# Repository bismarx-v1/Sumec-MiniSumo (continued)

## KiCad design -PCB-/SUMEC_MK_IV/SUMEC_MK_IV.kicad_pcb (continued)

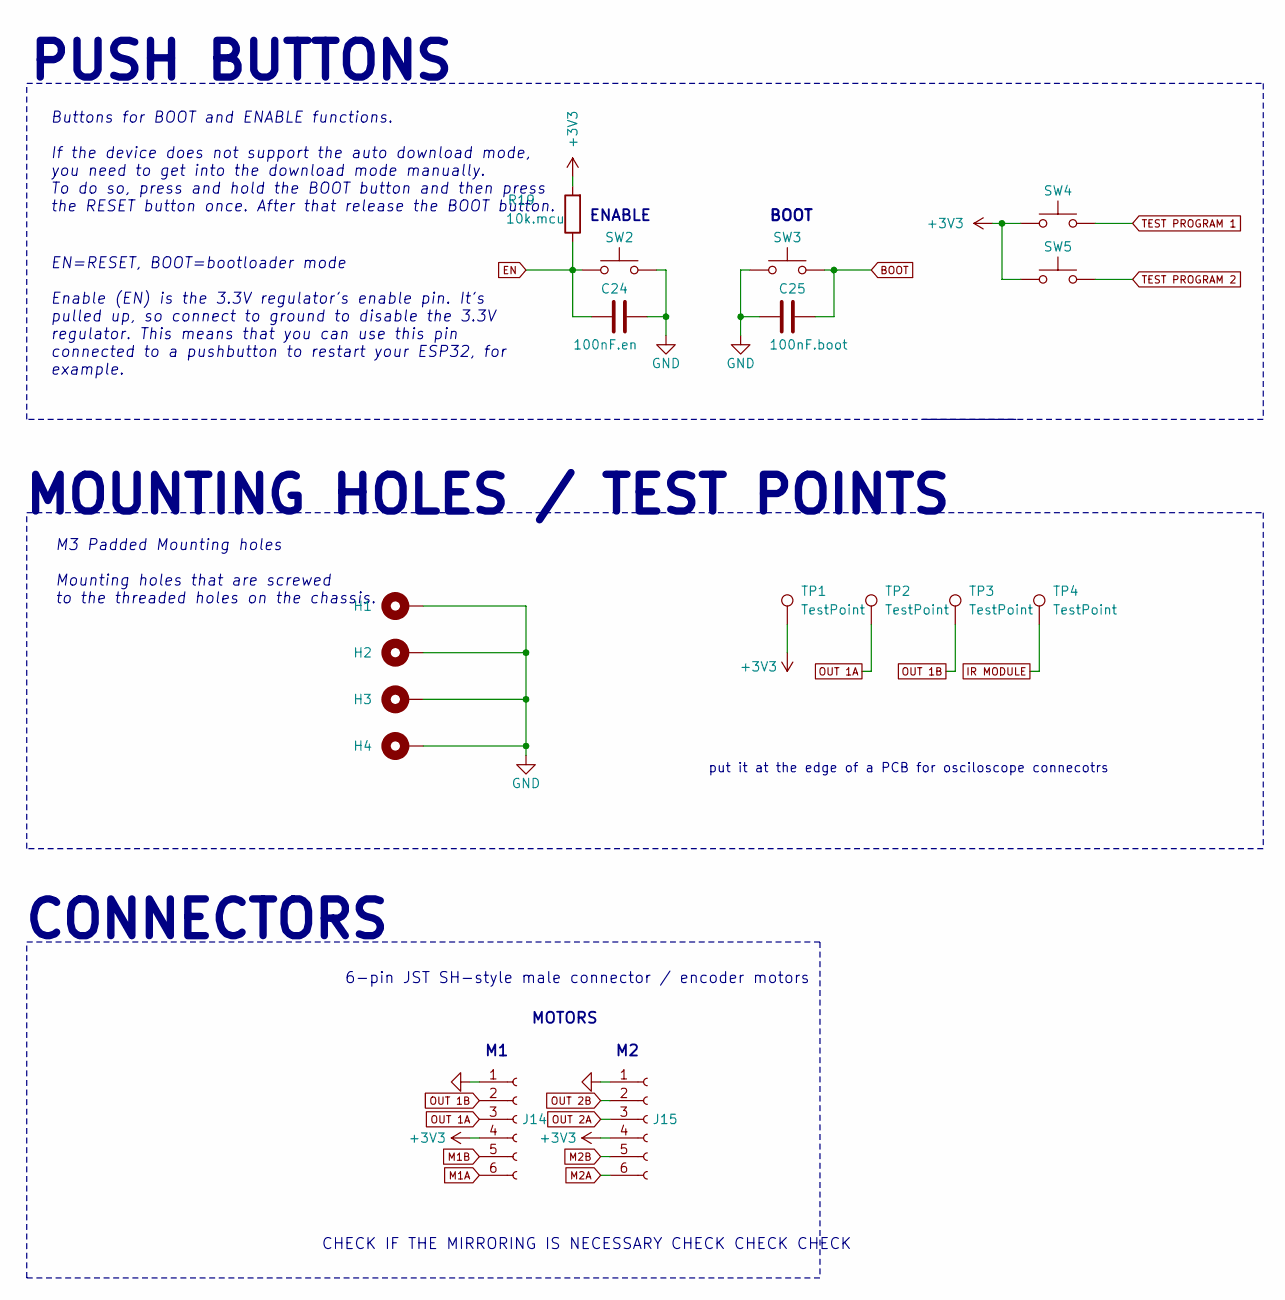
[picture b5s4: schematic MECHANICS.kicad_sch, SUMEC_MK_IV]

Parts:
C24: 100nF.en; C_0805_2012Metric_Pad1.18x1.45mm_HandSolder
C25: 100nF.boot; C_0805_2012Metric_Pad1.18x1.45mm_HandSolder
H1, H2, H3, H4: Mounting Hole M3; MountingHole_3.2mm_M3_Pad_Via
J14, J15: Conn_01x06_Socket; JST_SH_SM06B-SRSS-TB_1x06-1MP_P1.00mm_Horizontal
R19: 10k.mcu; R_0805_2012Metric_Pad1.20x1.40mm_HandSolder
SW2, SW3, SW4, SW5: SW_Push; SW_SPST_EVQPE1
TP1, TP2, TP3, TP4: TestPoint; TestPoint_Pad_1.0x1.0mm

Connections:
+3V3: J14.4, J15.4, R19.2, SW4.1, SW5.1, TP1.1; also elsewhere on the board
BOOT: C25.1, SW3.2; also elsewhere on the board
EN: C24.1, R19.1, SW2.2; also elsewhere on the board
GND: C24.2, C25.2, H1.1, H2.1, H3.1, H4.1, J14.1, J15.1, SW2.1, SW3.1; also elsewhere on the board
IR MODULE: TP4.1; also elsewhere on the board
M1A: J14.6; also elsewhere on the board
M1B: J14.5; also elsewhere on the board
M2A: J15.6; also elsewhere on the board
M2B: J15.5; also elsewhere on the board
OUT 1A: J14.3, TP2.1; also elsewhere on the board
OUT 1B: J14.2, TP3.1; also elsewhere on the board
OUT 2A: J15.3; also elsewhere on the board
OUT 2B: J15.2; also elsewhere on the board
TEST PROGRAM 1: SW4.2; also elsewhere on the board
TEST PROGRAM 2: SW5.2; also elsewhere on the board

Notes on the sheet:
put it at the edge of a PCB for osciloscope connecotrs
PUSH BUTTONS
CHECK IF THE MIRRORING IS NECESSARY CHECK CHECK CHECK
M3 Padded Mounting holes Mounting holes that are screwed to the threaded holes on the chassis.
ENABLE
EN=RESET, BOOT=bootloader mode Enable (EN) is the 3.3V regulator's enable pin. It's pulled up, so connect to ground to disable the 3.3V regulator. This means that you can use this pin connected to a pushbutton to restart your ESP32, for example.
Buttons for BOOT and ENABLE functions. If the device does not support the auto download mode, you need to get into the download mode manually. To do so, press and hold the BOOT button and then press the RESET button once. After that release the BOOT button.
BOOT
CONNECTORS
6-pin JST SH-style male connector / encoder motors
MOUNTING HOLES / TEST POINTS
MOTORS

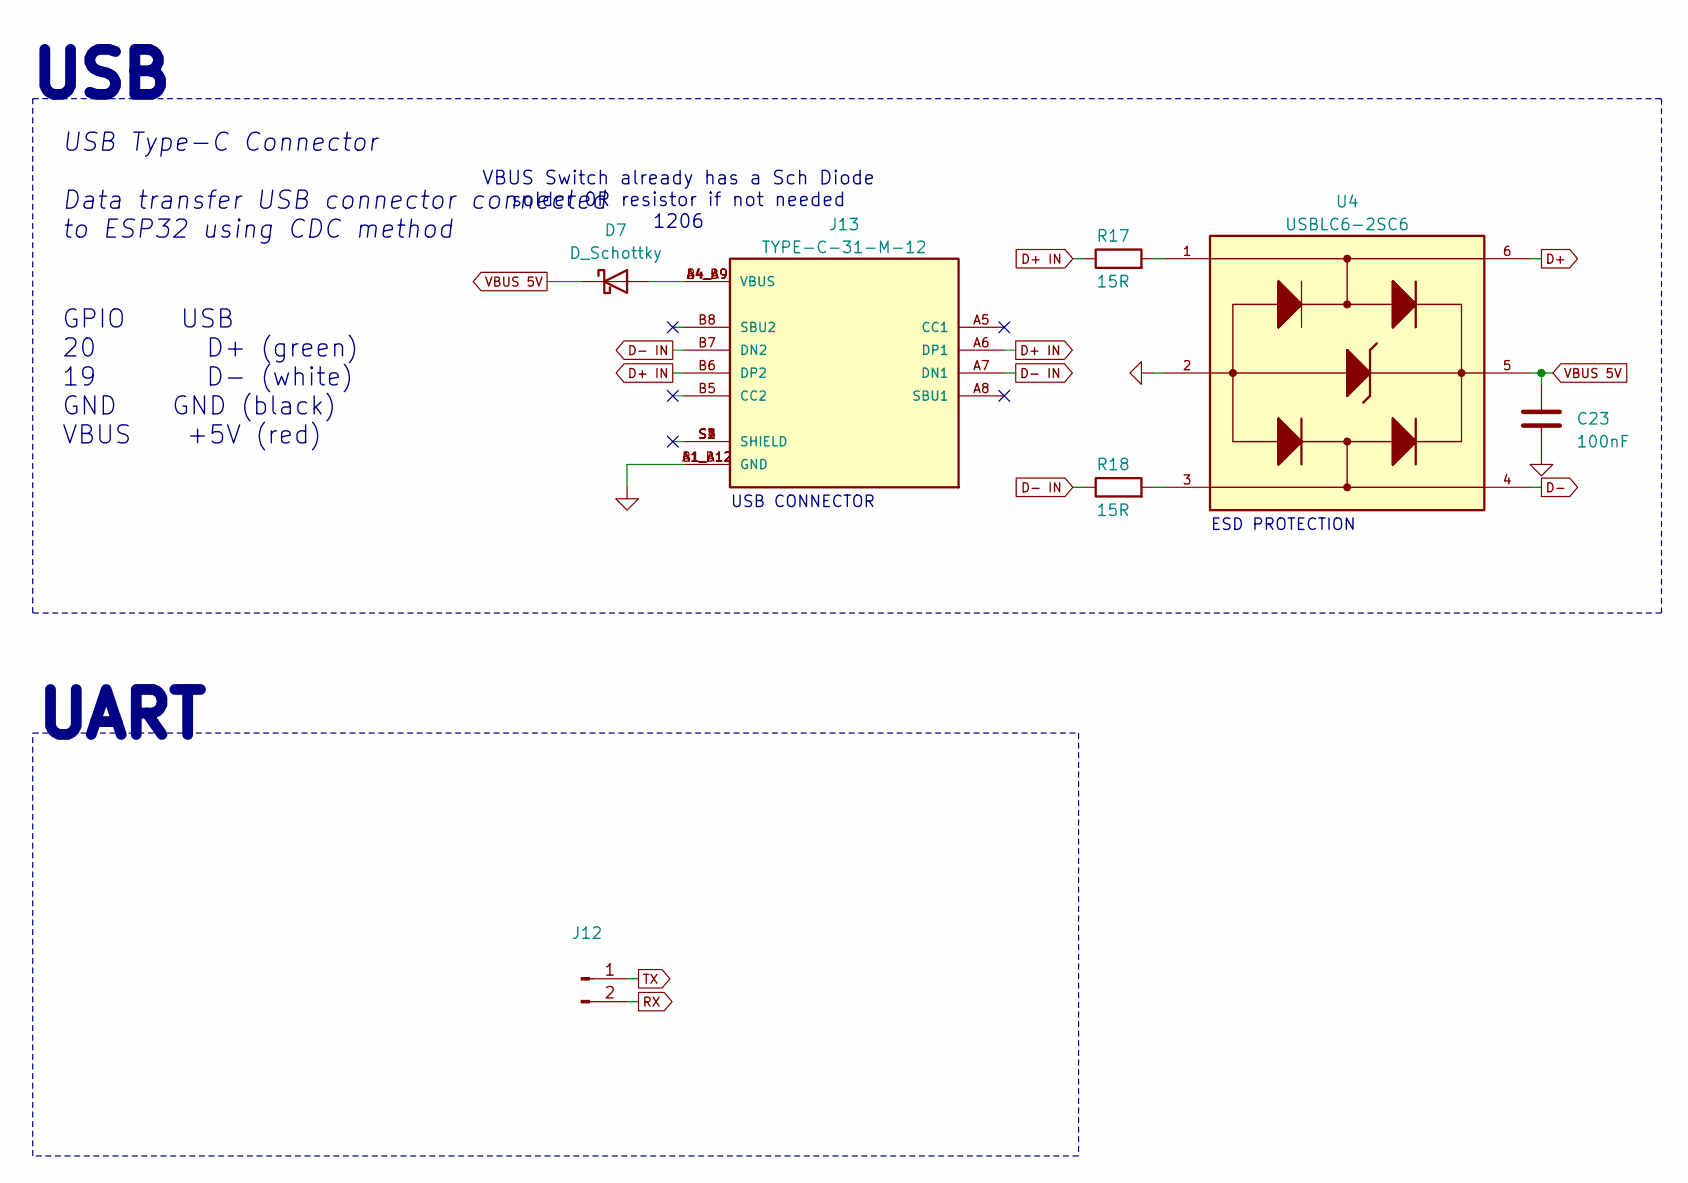
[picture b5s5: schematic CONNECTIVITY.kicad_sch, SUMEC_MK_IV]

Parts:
C23: 100nF; C_0805_2012Metric_Pad1.18x1.45mm_HandSolder
D7: D_Schottky; D_1206_3216Metric_Pad1.42x1.75mm_HandSolder
J12: Conn_01x02_Pin; TestPoint_2Pads_Pitch2.54mm_Drill0.8mm
J13: TYPE-C-31-M-12; USB_Type_C; PARTREV 2020.12.08
R17, R18: 15R; R_0805_2012Metric_Pad1.20x1.40mm_HandSolder
U4: USBLC6-2SC6; TSOT-23-6_HandSoldering

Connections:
D+: U4.6; also elsewhere on the board
D+ IN: J13.A6 (DP1), J13.B6 (DP2), R17.1
D-: U4.4; also elsewhere on the board
D- IN: J13.A7 (DN1), J13.B7 (DN2), R18.1
GND: C23.2, J13.A1_B12 (GND), J13.B1_A12 (GND), U4.2; also elsewhere on the board
unnamed: D7.2 (A), J13.A4_B9 (VBUS), J13.B4_A9 (VBUS)
unnamed: R17.2, U4.1
unnamed: R18.2, U4.3
RX: J12.2; also elsewhere on the board
TX: J12.1; also elsewhere on the board
VBUS 5V: C23.1, D7.1 (K), U4.5; also elsewhere on the board

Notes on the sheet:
VBUS Switch already has a Sch Diode solder 0R resistor if not needed 1206
USB
GPIO USB 20 D+ (green) 19 D- (white) GND GND (black) VBUS +5V (red)
USB CONNECTOR
USB Type-C Connector Data transfer USB connector connected to ESP32 using CDC method
UART
ESD PROTECTION

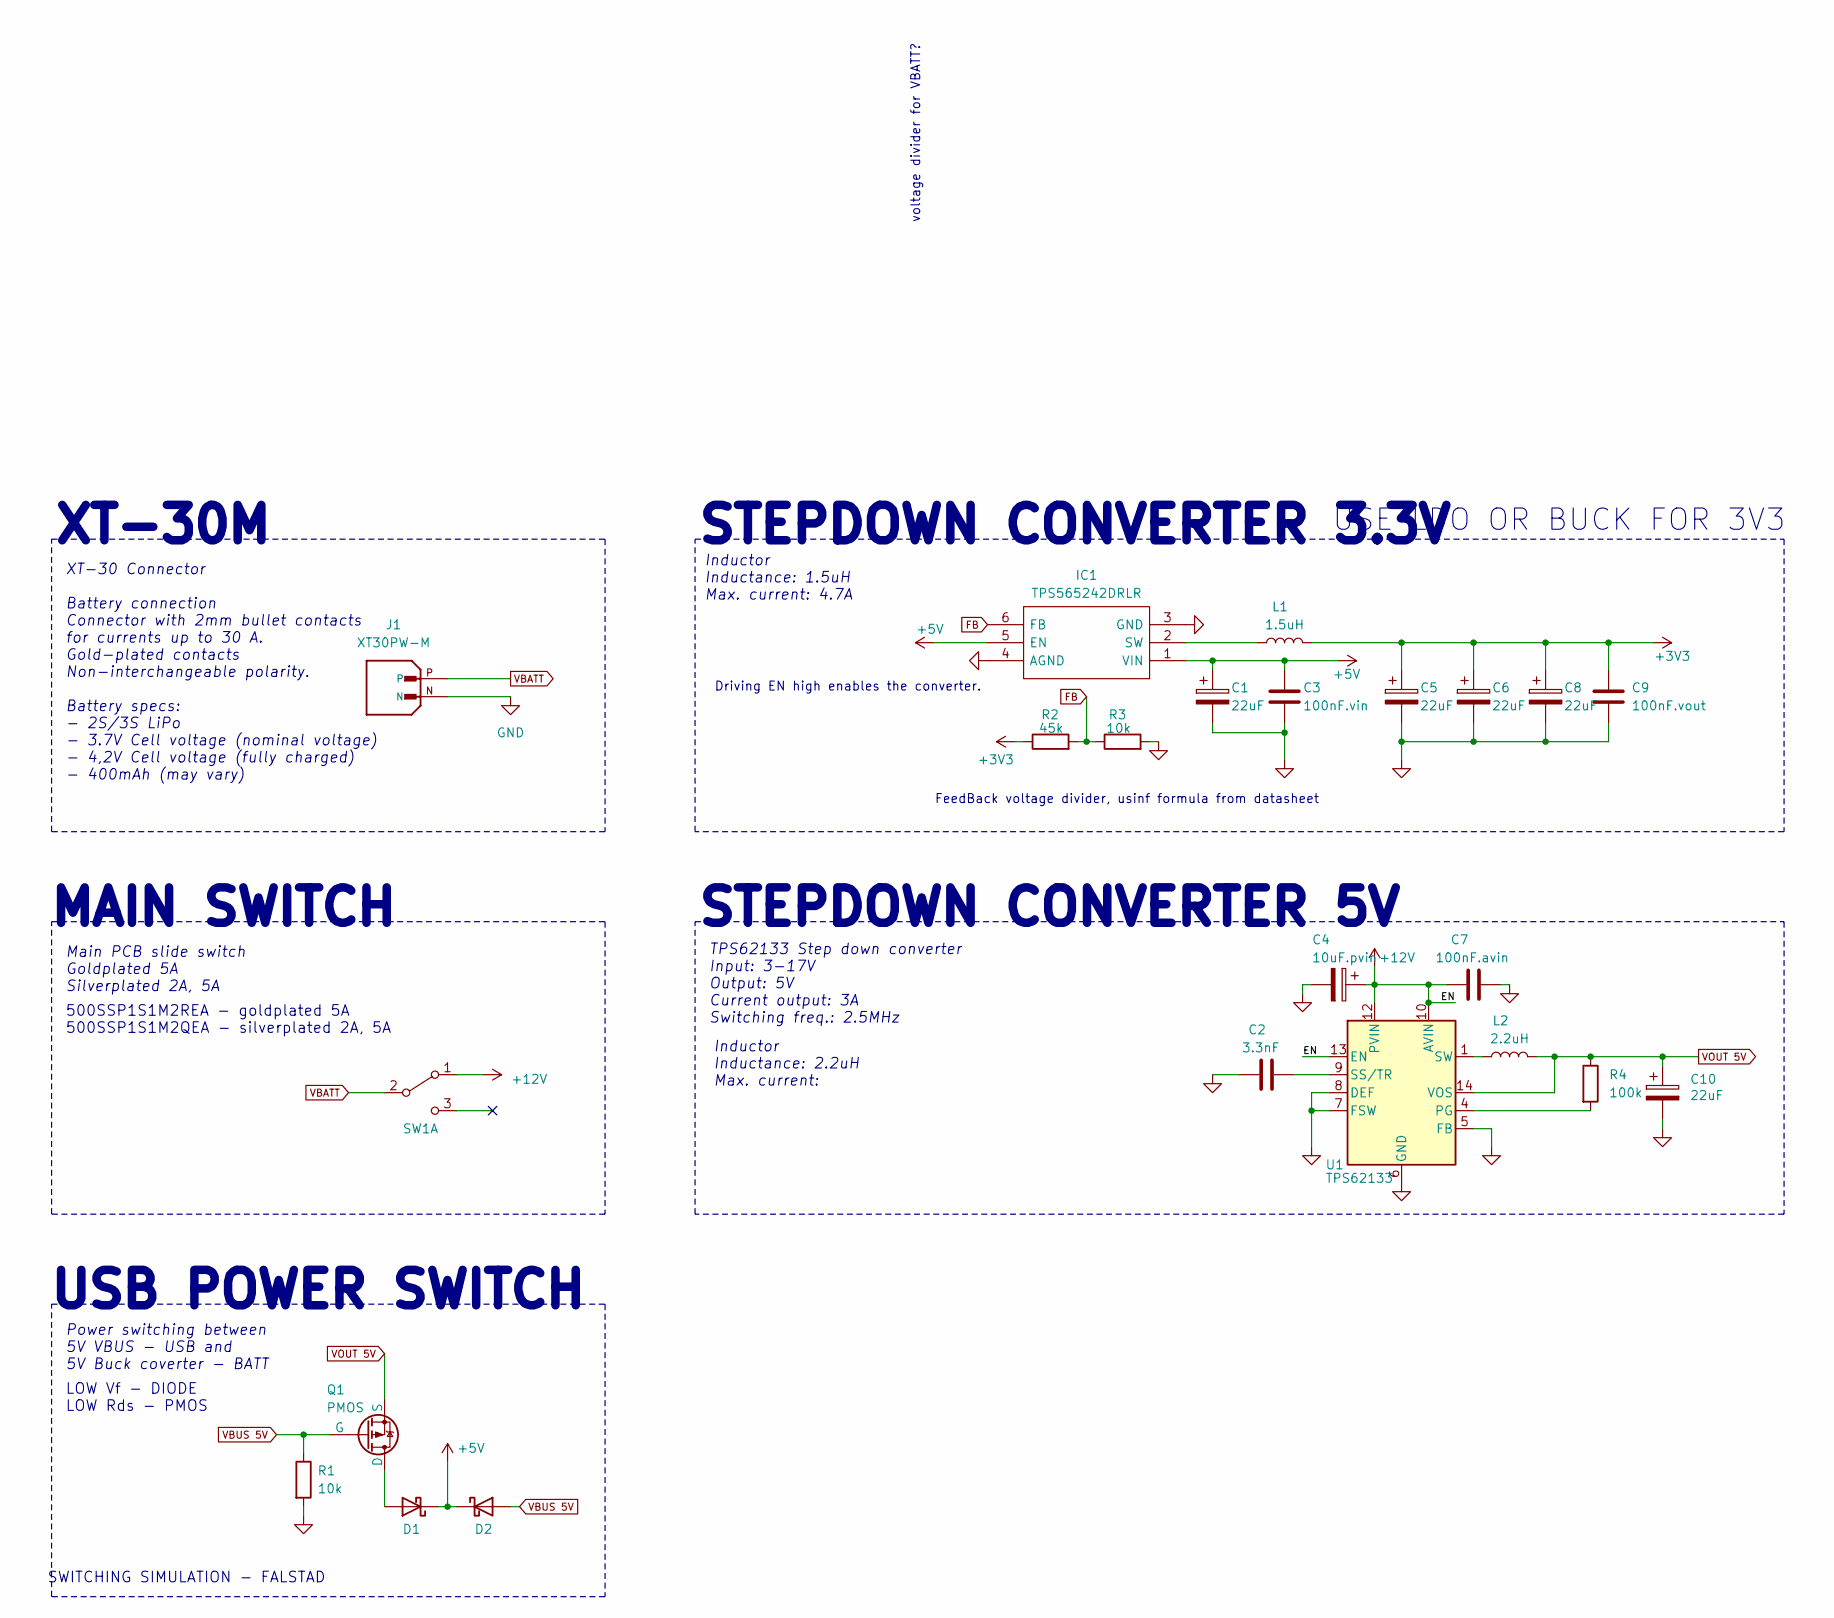
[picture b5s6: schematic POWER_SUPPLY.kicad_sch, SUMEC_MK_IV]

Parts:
C1, C5, C6, C8, C10: 22uF; CP_EIA-2012-12_Kemet-R_Pad1.30x1.05mm_HandSolder
C2: 3.3nF; C_0805_2012Metric_Pad1.18x1.45mm_HandSolder
C3: 100nF.vin; C_0805_2012Metric_Pad1.18x1.45mm_HandSolder; LCSC C49678
C4: 10uF.pvin; CP_EIA-3216-18_Kemet-A_Pad1.58x1.35mm_HandSolder
C7: 100nF.avin; C_0805_2012Metric_Pad1.18x1.45mm_HandSolder
C9: 100nF.vout; C_0805_2012Metric_Pad1.18x1.45mm_HandSolder; LCSC C49678
D1, D2: D_Schottky; D_1206_3216Metric_Pad1.42x1.75mm_HandSolder
IC1: TPS565242DRLR; SOT-563; Manufacturer_Part_Number TPS565242DRLR; Mouser Part Number 595-TPS565242DRLR
J1: XT30PW-M; PARTREV 1.2
L1: 1.5uH; L_Vishay_IHLP-1212
L2: 2.2uH; L_Vishay_IHLP-1616
Q1: PMOS; SOT-23-3
R1: 10k; R_0805_2012Metric_Pad1.20x1.40mm_HandSolder
R2: 45k; R_0805_2012Metric_Pad1.20x1.40mm_HandSolder; LCSC C17470
R3: 10k; R_0805_2012Metric_Pad1.20x1.40mm_HandSolder; LCSC C17633
R4: 100k; R_0805_2012Metric_Pad1.20x1.40mm_HandSolder
SW1: SW_DPDT_x2; Custom_SPDT_4.7mm_Switch
U1: TPS62133; VQFN-16-1EP_3x3mm_P0.5mm_EP1.68x1.68mm_ThermalVias

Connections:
+3V3: C5.1, C6.1, C8.1, C9.1, L1.2, R2.1; also elsewhere on the board
+5V: C1.1, C3.1, D1.1 (K), D2.1 (K), IC1.1 (VIN), IC1.5 (EN); also elsewhere on the board
+12V: C4.1, C7.1, SW1.1 (A), U1.10 (AVIN), U1.11 (PVIN), U1.12 (PVIN), U1.13 (EN); also elsewhere on the board
FB: IC1.6 (FB), R2.2, R3.1
GND: C1.2, C2.1, C3.2, C4.2, C5.2, C6.2, C7.2, C8.2, C9.2, C10.2, IC1.3 (GND), IC1.4 (AGND), J1.N, R1.2, R3.2, U1.5 (FB), U1.6 (GND), U1.7 (FSW), U1.8 (DEF), U1.15 (GND), U1.16 (GND), U1.17 (GND); also elsewhere on the board
unnamed: D1.2 (A), Q1.1 (D)
unnamed: IC1.2 (SW), L1.1
unnamed: L2.1, U1.1 (SW), U1.2 (SW), U1.3 (SW)
unnamed: R4.2, U1.4 (PG)
unnamed: C2.2, U1.9 (SS/TR)
VBATT: J1.P, SW1.2 (B)
VBUS 5V: D2.2 (A), Q1.2 (G), R1.1; also elsewhere on the board
VOUT 5V: C10.1, L2.2, Q1.3 (S), R4.1, U1.14 (VOS)

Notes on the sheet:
Inductor Inductance: 2.2uH Max. current:
SWITCHING SIMULATION - FALSTAD
Driving EN high enables the converter.
USB POWER SWITCH
XT-30M
LOW Vf - DIODE LOW Rds - PMOS
Power switching between 5V VBUS - USB and 5V Buck coverter - BATT
MAIN SWITCH
voltage divider for VBATT?
500SSP1S1M2REA - goldplated 5A 500SSP1S1M2QEA - silverplated 2A, 5A
Main PCB slide switch Goldplated 5A Silverplated 2A, 5A
STEPDOWN CONVERTER 3.3V
STEPDOWN CONVERTER 5V
Inductor Inductance: 1.5uH Max. current: 4.7A
TPS62133 Step down converter Input: 3-17V Output: 5V Current output: 3A Switching freq.: 2.5MHz
FeedBack voltage divider, usinf formula from datasheet
XT-30 Connector Battery connection Connector with 2mm bullet contacts for currents up to 30 A. Gold-plated contacts Non-interchangeable polarity. Battery specs: - 2S/3S LiPo - 3.7V Cell voltage (nominal voltage) - 4,2V Cell voltage (fully charged) - 400mAh (may vary)
USE LDO OR BUCK FOR 3V3

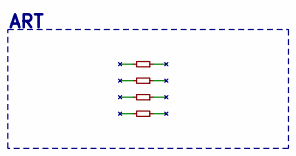
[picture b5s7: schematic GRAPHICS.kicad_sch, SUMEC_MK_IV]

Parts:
R20: R; purosidenegative
R21: R; SPS LOGO
R22: R; boi
R23: R; Logo

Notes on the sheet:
ART

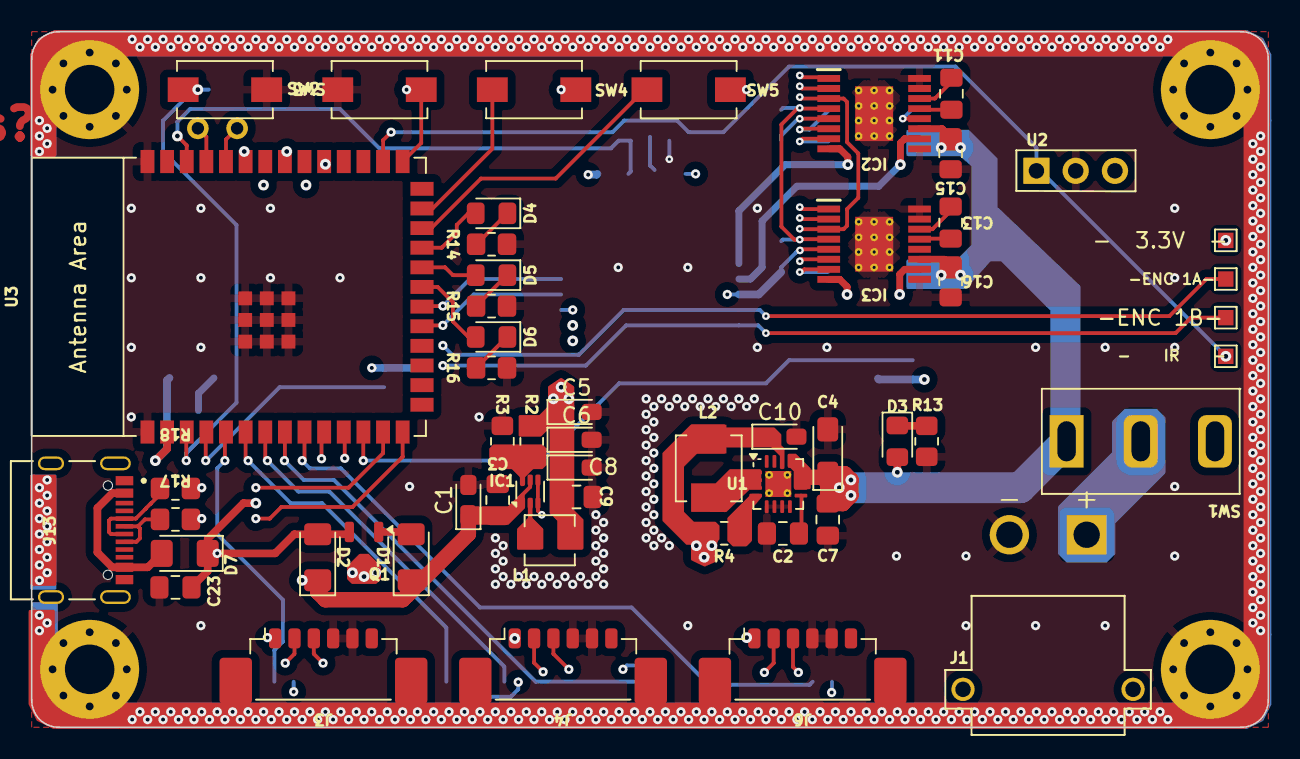
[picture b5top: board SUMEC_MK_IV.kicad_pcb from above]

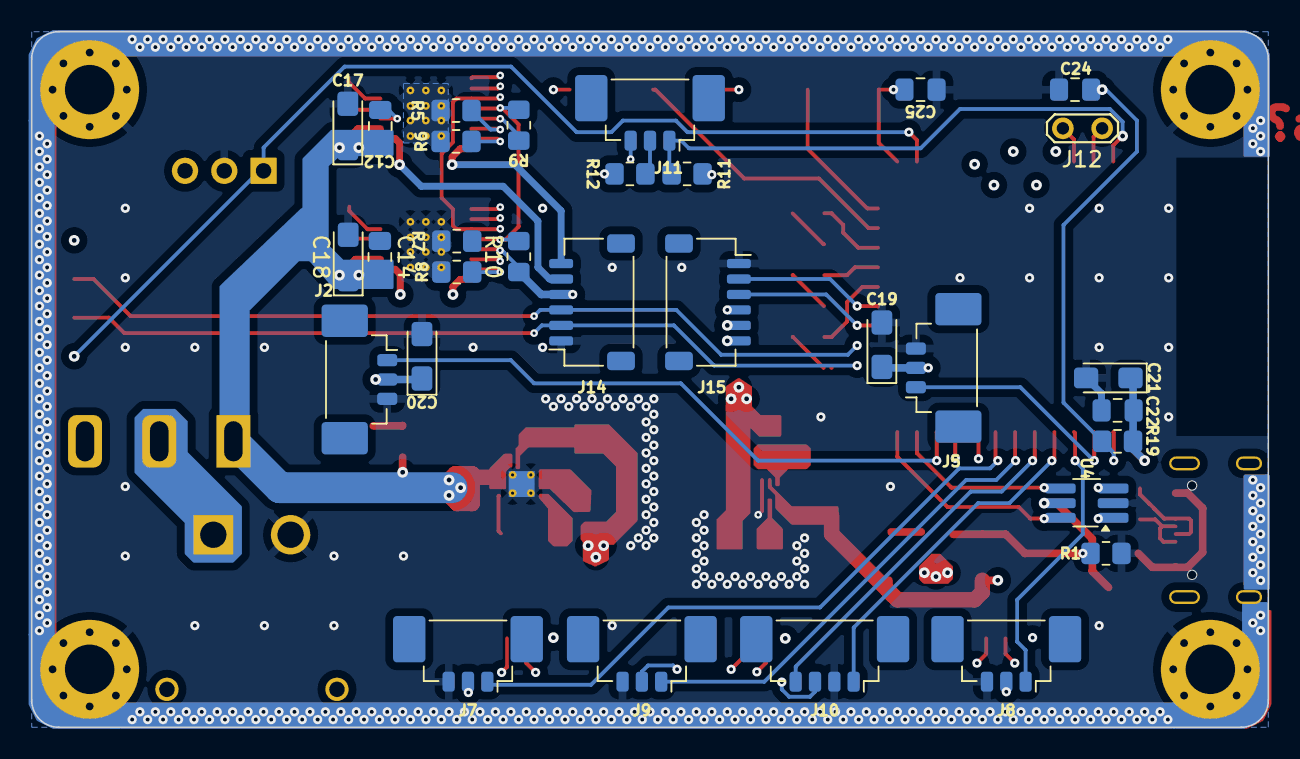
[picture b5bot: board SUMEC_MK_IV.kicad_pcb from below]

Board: 4 copper layers, 80.0 x 45.0 mm, 93 parts (31 on the bottom side), 68 nets.

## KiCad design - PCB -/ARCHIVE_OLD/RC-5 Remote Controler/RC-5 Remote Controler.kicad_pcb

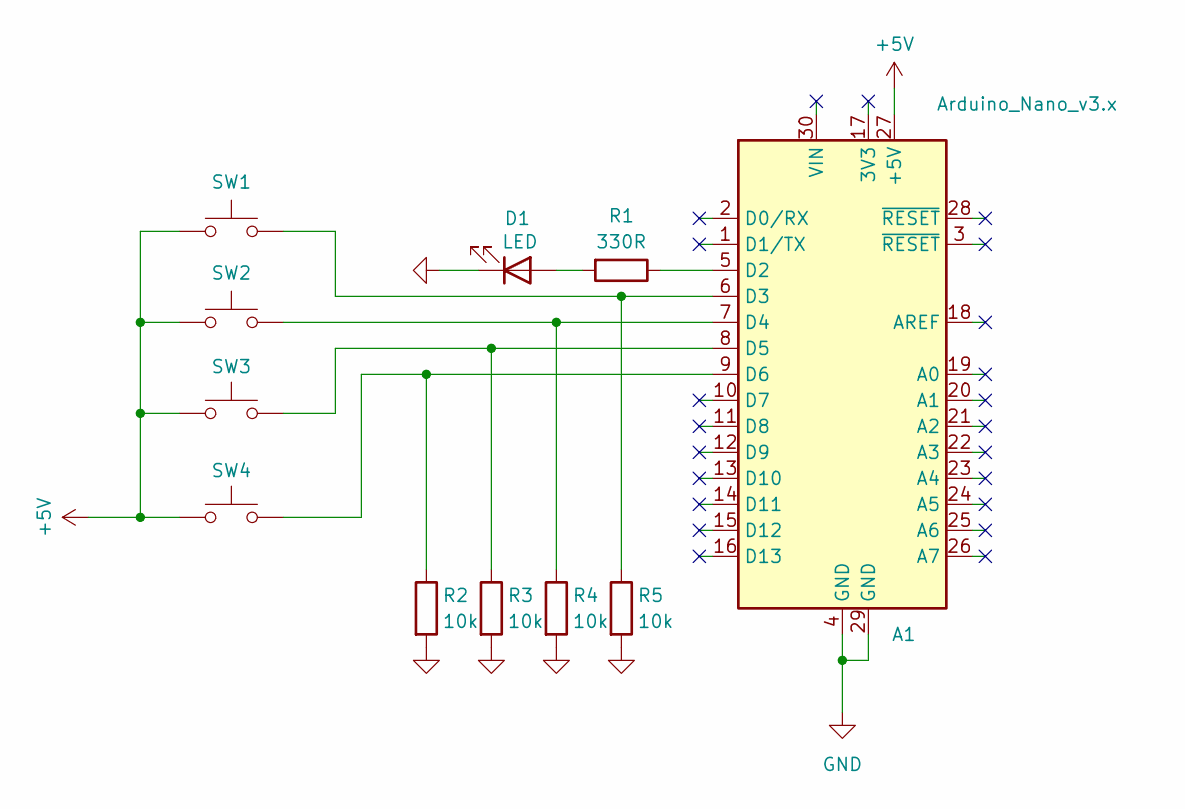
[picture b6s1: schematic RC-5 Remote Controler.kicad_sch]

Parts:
A1: Arduino_Nano_v3.x; Arduino_Nano
D1: LED; LED_D3.0mm_Horizontal_O3.81mm_Z6.0mm
R1: 330R; R_Axial_DIN0207_L6.3mm_D2.5mm_P10.16mm_Horizontal
R2, R3, R4, R5: 10k; R_Axial_DIN0207_L6.3mm_D2.5mm_P10.16mm_Horizontal
SW1, SW2, SW3, SW4: SW_Push; SW_PUSH_6mm

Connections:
+5V: A1.27 (+5V), SW1.1, SW2.1, SW3.1, SW4.1
GND: A1.4 (GND), A1.29 (GND), D1.1 (K), R2.2, R3.2, R4.2, R5.2
unnamed: A1.5 (D2), R1.1
unnamed: A1.6 (D3), R5.1, SW1.2
unnamed: A1.7 (D4), R4.1, SW2.2
unnamed: A1.8 (D5), R3.1, SW3.2
unnamed: A1.9 (D6), R2.1, SW4.2
unnamed: D1.2 (A), R1.2

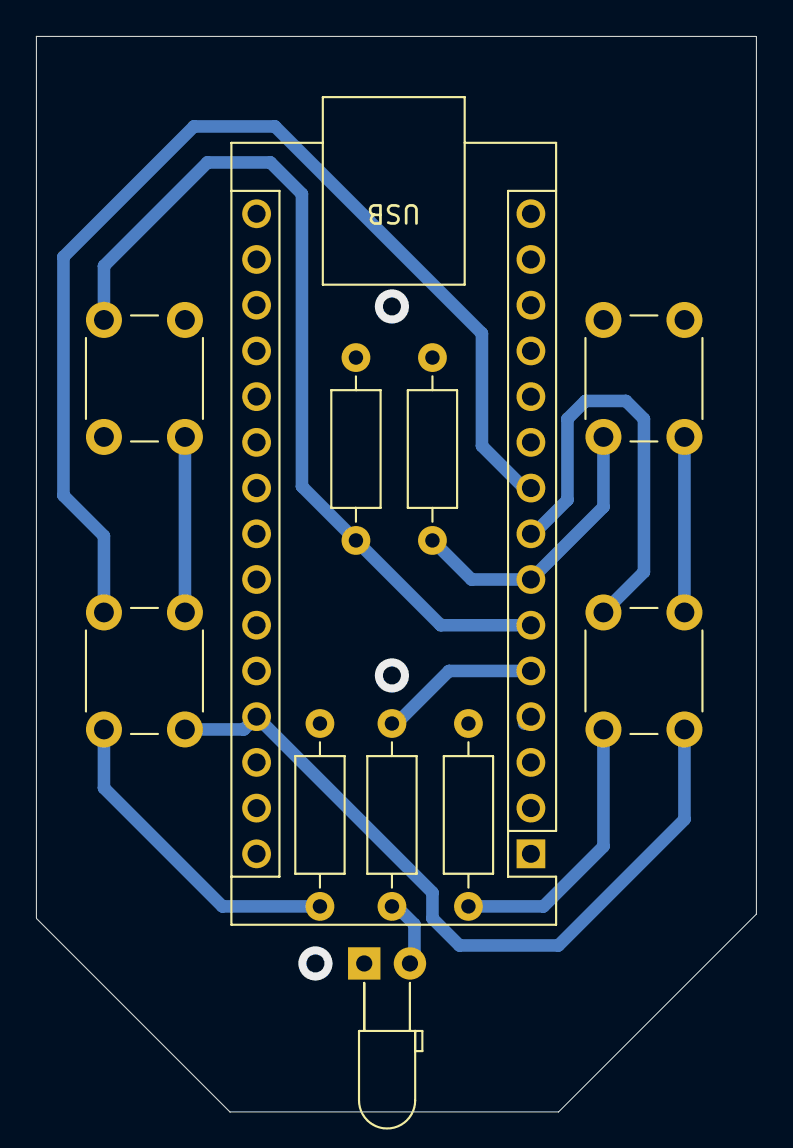
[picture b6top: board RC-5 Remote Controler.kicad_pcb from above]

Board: 2 copper layers, 40.0 x 59.8 mm, 11 parts (0 on the bottom side), 8 nets.

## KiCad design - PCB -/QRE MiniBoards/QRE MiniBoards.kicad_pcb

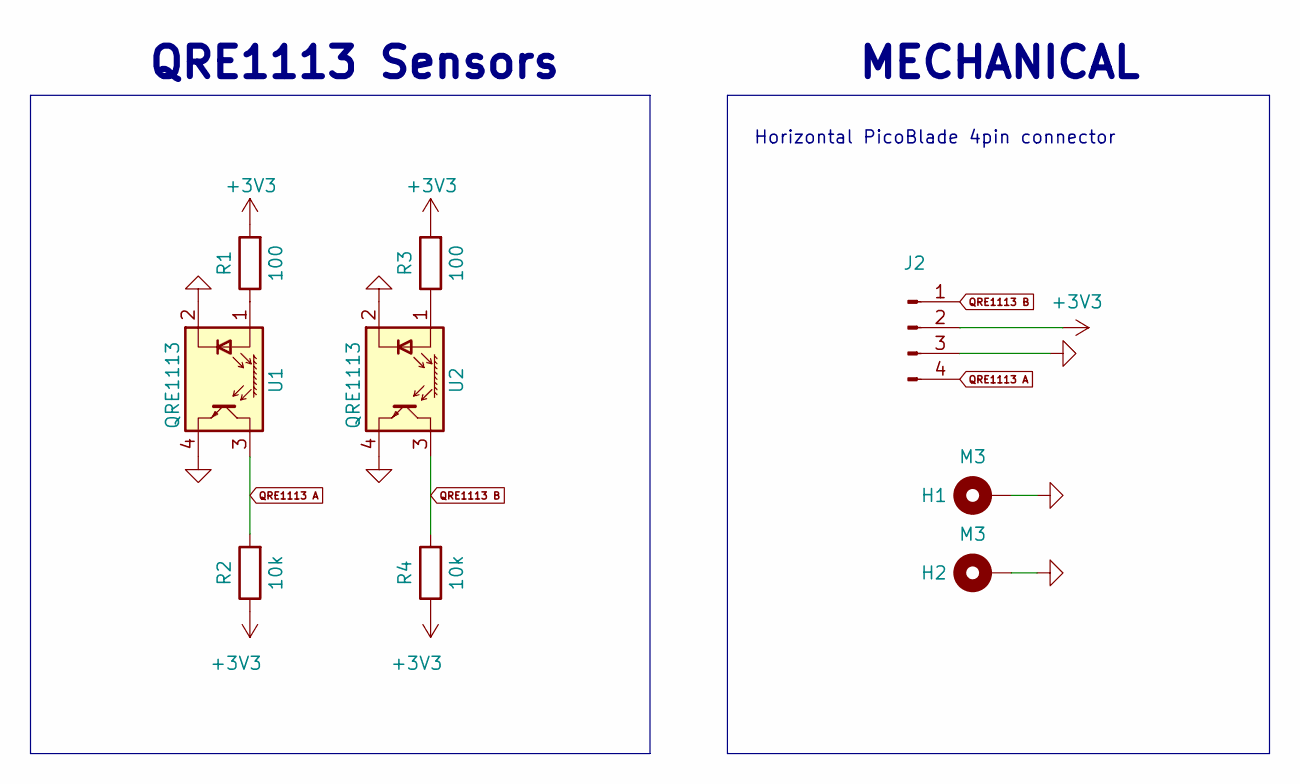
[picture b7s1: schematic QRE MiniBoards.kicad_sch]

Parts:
H1, H2: M3; MountingHole_3.2mm_M3_Pad
J2: Conn_01x04_Pin; Molex_PicoBlade_53261-0471_1x04-1MP_P1.25mm_Horizontal
R1, R3: 100; R_0805_2012Metric_Pad1.20x1.40mm_HandSolder
R2, R4: 10k; R_0805_2012Metric_Pad1.20x1.40mm_HandSolder
U1, U2: QRE1113; OnSemi_CASE100AQ - QRE1113

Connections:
+3V3: J2.2, R1.2, R2.1, R3.2, R4.1
GND: H1.1, H2.1, J2.3, U1.2 (K), U1.4, U2.2 (K), U2.4
unnamed: R1.1, U1.1 (A)
unnamed: R3.1, U2.1 (A)
QRE1113 A: J2.4, R2.2, U1.3
QRE1113 B: J2.1, R4.2, U2.3

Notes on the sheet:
QRE1113 Sensors
Horizontal PicoBlade 4pin connector
MECHANICAL

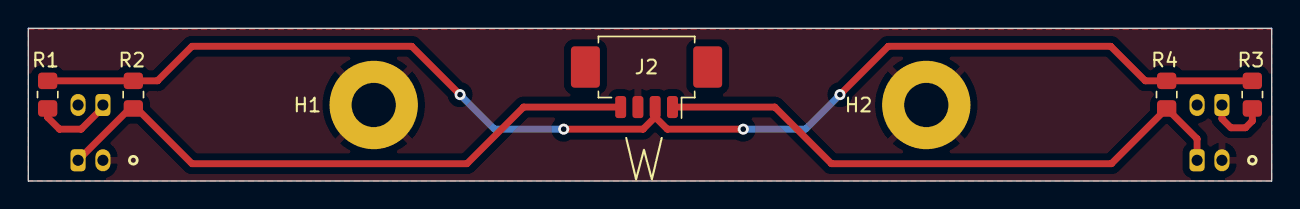
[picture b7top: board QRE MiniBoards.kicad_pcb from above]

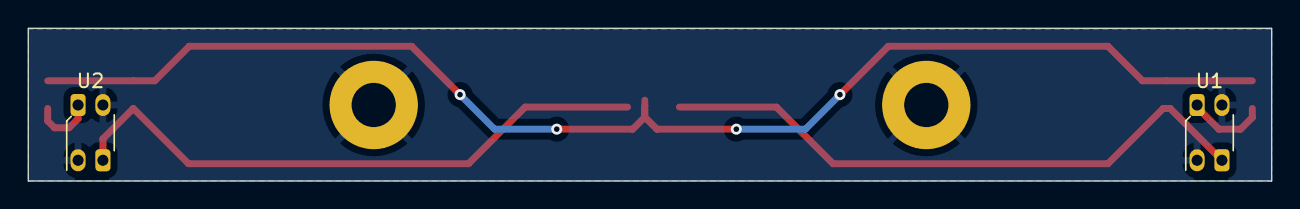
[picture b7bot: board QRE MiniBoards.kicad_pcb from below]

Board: 2 copper layers, 90.0 x 11.0 mm, 9 parts (2 on the bottom side), 6 nets.

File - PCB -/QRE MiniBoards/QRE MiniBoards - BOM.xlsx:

Item | Qty | Reference(s) | Value | LibPart | Footprint | Link
1 | 2 | H1, H2 | M3 | MountingHole - Pad (GND) | MountingHole:MountingHole_3.2mm_M3_Pad | N/A
2 | 1 | J2 | Conn_01x04 | MOLEX PicoBlade 4pin | Connector_Molex:Molex_PicoBlade_53398-0471_1x04-1MP_P1.25mm_Vertical
3 | 2 | R1, R3 | 100R | Resistor SMD | Resistor_SMD:R_1206_3216Metric_Pad1.30x1.75mm_HandSolder
4 | 2 | R2, R4 | 10k | Resistor SMD | Resistor_SMD:R_1206_3216Metric_Pad1.30x1.75mm_HandSolder
5 | 2 | U1, U2 | N/A | QRE1113 THT | sumec_library:OnSemi_CASE100AQ - QRE1113
6
7 | 9
8
9
10
11
12
13
14
15
16
17
18
19
20
21
22
23
24
25
26
27
28
29
30
31
32
33
34
35

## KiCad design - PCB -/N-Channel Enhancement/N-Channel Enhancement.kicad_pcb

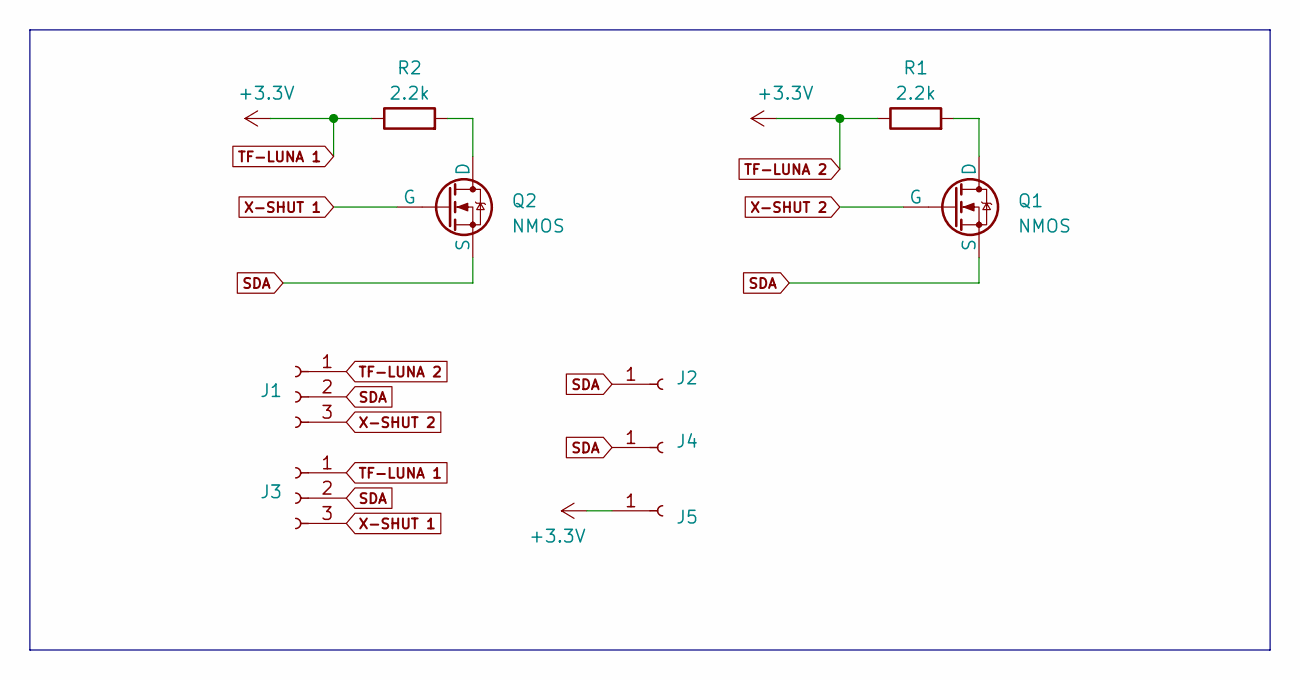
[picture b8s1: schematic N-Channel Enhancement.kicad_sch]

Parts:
J1, J3: Conn_01x03_Socket; PinSocket_1x03_P2.54mm_Vertical
J2, J4, J5: Conn_01x01_Socket; PinSocket_1x01_P2.54mm_Vertical
Q1, Q2: NMOS; SOT-23
R1, R2: 2.2k; R_Axial_DIN0207_L6.3mm_D2.5mm_P10.16mm_Horizontal

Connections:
unnamed: Q1.1 (D), R1.2
unnamed: Q2.1 (D), R2.2
SDA: J1.2, J2.1, J3.2, J4.1, Q1.3 (S), Q2.3 (S)
TF-LUNA 1: J1.1, J3.1, J5.1, R1.1, R2.1
X-SHUT 1: J3.3, Q2.2 (G)
X-SHUT 2: J1.3, Q1.2 (G)

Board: 2 copper layers, 9 parts (2 on the bottom side), 6 nets, no tracks yet.

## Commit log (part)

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2024-03-27 Driver test fix; Qre and Sharp libs pinMode fix
2024-03-27 tf-l set address and factory reset work, read and read distance do not
2024-03-28 qre_motors
2024-03-28 Fixed wrong value in a comment
2024-03-29 Čištění-github-CODE-mám zalohu
2024-03-29 NEW main code
2024-03-29 přidán hlavičkový soubor pro piny a proměné
2024-03-29 dodělání hlavičkového souboru pinů a proměných
2024-03-30 přidány třídy, zatím neupravené
2024-04-02 ring defence
2024-04-03 nahravani
2024-04-04 Ring_program
2024-04-04 bom update
2024-04-05 zpravení Tiku
2024-04-06 Robotic arena rules
2024-04-06 alalalalaallalllalalala
2024-04-08 přesun zpoždění do stavů
2024-04-09 SMD After BOM Update
2024-04-09 + stl koleček
2024-04-12 + IRstart
2024-04-12 L_motors
2024-04-12 úprava mainu
2024-04-15 aktualni program
2024-04-15 SMD After Rybnik BOM
2024-04-18 přesun Mainu do branche New_Code_branch
2024-04-18 + Strong program
2024-04-18 + sharpy
2024-04-18 + ~sharpy~
2024-04-19 Tick_A => Tick_QRE
2024-04-19 předělání motorů zpět, +přejmenování pinsAndVariables => variablesForMAIN
2024-04-19 přesun rozhodnutí střední luny na state 7
2024-04-19 added general turning methods
2024-04-20 added isStopped function to DohyoID
2024-04-20 added resume when unknown protocol detected
2024-04-20 úprava Lun
2024-04-20 corrected typo
2024-04-20 uložení IR problému da readme filu
2024-04-20 + chybová hláška IR-RC5 - Wroclaw
2024-04-23 sharpy zpět
2024-04-23 Funkční: nevyjetí z ringu, Luny, Sharpy
2024-04-23 fotky
2024-04-23 úklid main codu a souboru s proměnými
2024-04-24 úprava ledek
2024-04-25 Updated schematic
2024-04-29 PCB schematic update
2024-05-02 remote pcb
2024-05-02 minor change
2024-05-08 Remote PCB , rebuild update
2024-05-09 not fully working code for sending udp packets both ways between sumec and a pc or phone. python script for the pc side is not provided (yet), use any udp reciever app
2024-05-10 Jedobot - program na soutěži
2024-05-10 Nákresy plechu
2024-05-14 code has an error with creating callbacks when using a class instead of plain functions. don't know how to fix it but the rest works
2024-05-14 backup automatic delete
2024-05-20 PCB edit
2024-05-20 Some improvements
    programming button moved
2024-05-21 old commit. don't know what was going on, i just know it doesn't work as a lib, and does work as a file full of functions.
2024-05-22 Minor PCB and Schematic updates
2024-05-22 box flex parts STLs
2024-05-23 mere and better comments explaining the bug
2024-06-07 DC-DC Converter
2024-06-07 Gerber Export
2024-06-08 Remote final changes
2024-06-09 Final final update and order
2024-06-17 New_code-function_basic
2024-06-17 starting with out of line situation
2024-06-18 Sensors update
2024-06-18 Sumec optics final update
2024-06-24 dodelani sharpu
2024-06-26 dont know. just progress save. sowwy :3
2024-06-27 Last update
2024-06-28 last save before release
2024-06-30 Archive creation
2024-07-01 Start of DRV Breakout board
    should be an easy one
2024-07-01 start of: SUMEC_MK_IV
2024-07-01 MK_IV update
2024-07-01 github cleanup. folder renaming. pcb folder cleanup.
    Pics do not belong in github, dont worry, still have them on my machine.
2024-07-04 i did, something (archive return but now its better)
2024-07-05 MK4 schematic update
2024-07-05 at the crib, straight up "working it" and by "it" hehe, lets just say, my KiCADIS
2024-07-08 DC-DC conv added
2024-07-08 added stab. VBUS, USB connection
2024-07-09 power supp small change
2024-07-11 MK_IV update
    Power supp sheet done, mechanical sheet almost done, some changes, updates etc.
2024-07-11 MKIV update
    Motor driver schematic update
2024-07-13 MK4 schematic update
    Almost done. Did some work on motor drivers, should be final now. Sensors sheet is almost done - object detecting missing. MCU sheet - missing. but yeah. almost done.
2024-07-15 MKIV major update
    Updated everything, custom symbol for ESP32, MCU sheet done, new test points added, motor control revision.
    all left is to clean it up a bit
2024-07-16 3v3 buck redesign
2024-07-24 fixed typos
2024-07-26 just silly nothing-update
2024-07-27 Footprints added
2024-07-29 MK_IV PCB update
2024-07-30 MK_IV layout update
2024-07-31 PCB routing
2024-08-01 Small PCB routing
2024-08-02 PCB update
    (should I start over? Can I make it better)
2024-08-05 v3.0.9 SUMEC PCB
    Ufff, so, basically a full rewrite of the PCB, check it our its pretty sick, I think
2024-08-07 PCB final update
2024-08-07 3D models + silscreen
2024-08-15 Renamed "- CODE -" to "-CODE-"
    Hope this breaks stuff. Hate you all. ^w^
2024-08-15 Deletion of old PDF
2024-08-16 Flashing the remote from VSCode using the UNO as SPI programmer
    README_FlashingTheRemote.html
    - File explaining what we did
    platformio.ini
    - "Upgraded" .ini file
    main.cpp
    - just a blinking LED
2024-08-18 wroom 2 symbol
2024-08-20 a small cleanup
    UseThisOneIThink.txt
    - nah, not it. file useless now
    Test1.ino
    - first test of flashing the remote. better method found, file useless now
    \-CODE-\Temp\SumecRemote\FlashTest\main\
    - directory and all in it is useless
2024-08-21 BOM + silkscreen
2024-08-21 PCB and BOM update
2024-08-21 BOM final update
2024-08-23 solderability update pcb
2024-08-24 New models, TSOP positioning
    new 3d models thx jonas
2024-08-25 new custom symbol
    using sumec lib for nowm ill switch to schrack later
2024-08-26 minor updates
2024-08-28 Moved REMOTE pcb from sumec repo to the remote
2024-08-28 zip for QRE MiniBoard release
2024-08-29 silkscreen Footprint addition
2024-08-30 Dimensions back and front, 3d models for footprints.
2024-09-03 PCB and BOM updates
    Added links to MK_IV bom
    Fixed PMOS position and same length USB traces
2024-09-04 DRV board
2024-09-05 Added teardrops
2024-09-05 font warning in schematic
2024-09-06 added mouser BOM
2024-09-06 add coments and remove unnecessary comands
2024-09-06 Calendar creation
    Added a word doc for Robotic tournaments for SUMEC and [line follower] to compete in.
2024-09-10 Free fall IMG
2024-09-15 5V stepdown converter PCB layout small redisign
2024-09-15 PCB note removed
2024-09-15 this file had a bit too long filepath and that might be a problem on some systems.
2024-09-15 Schematic and PCB update
    Schematic update:
    - Font adjustment
    - Block rearrangement
    PCB update
    - Silkscreen
    - Minor layout update
2024-09-16 converted to newer kicad version
2024-09-16 minor text changes
2024-09-16 minor silkscreen value rearrangement
2024-09-16 minor text update in schematic
    Updated wrong branch but its fixed now
2024-09-16 quick motor driver test
    self-documenting code. good luck *
    -Natani :3
2024-09-16 Board and schematic update.
    PMOS switch added, 3d .step file created
2024-09-18 moved to archive
    No need to release this
2024-09-19 PCB "MK4"
2024-09-19 pcb mount back clamp
2024-09-20 push buttons and some other shit
2024-09-20 quick include fixes
    now all example files (and the udp lib file) include the .cpp files instead of the .h
2024-09-20 Filepath change 3D model fix
2024-09-20 3d folder cleanig
2024-09-20 3d model, possible fix, test
2024-09-20 add wireless comunication
2024-09-21 silkscreen value rearangments
2024-09-21 USB Polyfuse change
2024-09-22 Some minor changes
    BOM update, checked for some pinouts, still some work to do
2024-09-24 generated gerber files
2024-09-24 Stopping with RC-5
2024-09-24 new readmes
    not much to say really. soeone should check those
2024-09-25 body .stl
2024-09-27 starting led repair
2024-09-29 test assembly .stl
2024-09-29 Update .gitignore
    added OldVersions filter
2024-09-29 PCB Update
    DRC fix with 3v3 stepdown
2024-09-29 Gerbers plotting
2024-09-30 new plots
2024-09-30 new fixed gerber
2024-10-02 file cleanup
2024-10-07 BOM update
    Reserve, Mouser and main BOM update
2024-10-08 Mouser bom update
2024-10-13 add Stop funkcion
2024-10-14 Graphics update
    nothing to look at
2024-10-14 3d viewer update
    tactile button, inducotrs
2024-10-15 file reorganisation
2024-10-15 Working part of the UDP rewrite. next up, the part that's needed but doesn't work.
2024-10-17 body for testing new pcb
2024-10-18 body redesing - front
2024-10-19 main body part sketch
2024-10-19 body-front_small_improvements
2024-10-20 UDP lib is complete, rewiev and pull, nya.
2024-10-20 side sensor mount
2024-10-21 add coments
2024-10-21 treatment of Start function
2024-10-22 edit Redme
2024-10-22 quick fix
2024-10-24 motor mount
2024-10-24 add Pasive strategy
2024-10-25 next update to pasive program
2024-10-25 fixing not going back
2024-10-27 USB footprint fix
2024-10-28 minor tweaks
2024-11-01 fix passive strategy
2024-11-03 new graphics folder
    Not much, just a new folder for kicad graphics
2024-11-04 graphics update
2024-11-08 editing passive strategy - in progress
2024-11-10 mainly Graphics update
2024-11-12 mesuring function is working muse be edited
2024-11-13 mesuring function not working again
2024-11-15 Motor control test - defined
2024-11-15 USB C - fix
2024-11-15 defined pins motor test + idk
2024-11-15 Schematic minor update
2024-11-15 mesuring function works and can changing program with button
2024-11-16 initial push
    code is not working
2024-11-17 PCB Mosfet trace fix, test points
2024-11-18 pwm out --test
    just a test
2024-11-18 little edit passive strategy
2024-11-19 initial commit of Schola Pregensis ring 50 cm diameter
2024-11-19 program lokes good
2024-11-19 rest of the last commit
2024-11-20 xt guard
2024-11-20 all fixed ready to export
2024-11-20 it works
    so i just measure the pulse length in microseconds using a timer. conversion to distance and a library-fication will come later, nya.
2024-11-21 conversion to cm added. Test accuracy.
    conversion to a more usable thing is next.
2024-11-22 calibration fixed
2024-11-27 edit some valuses for Skola pragensis
2024-11-27 pcb guard + tolerations
2024-11-28 UNTESTED CODE. Pwm lib release.
    It maybe works, someone(me) should test it.
2024-11-29 fix mistake with stopping on the line
2024-11-29 Jonas + Savva motor test code
2024-11-29 QRE working
2024-11-29 no changes
2024-12-01 new flex guard
2024-12-02 solved problem with Luna
2024-12-02 old files removal
2024-12-03 rewrite pins for motors
2024-12-03 PCB-guard (last minute battery holder)
2024-12-04 1 day beatwen Estonsko - good state
2024-12-06 day before Robotex
2024-12-07 competetion in estonia edit
2024-12-12 start of different PCBs
2024-12-13 Revert "day before Robotex"
    This reverts commit fc9f62016582e3195ded8e7cb8a1801acde2b5e7.
2024-12-13 Schematic PDFs - Nats issue fixed
2024-12-17 calibrateing
2024-12-19 Start module PCB update
2024-12-19 Silkscreen update IR module
2025-01-17 finished record class
2025-01-19 encoders are done (mostly)
    There is a linker error.
    Other than that the motors appear to work. The motors will overshoot at higher speeds but that shouldnt be an issue.
    TODO:
    - Wheel circumference should be set to the real value.
    - Encoder steps are set to 154, but I just eyeballed that. Replace with something more accurate?.
2025-01-23 finished black box class
2025-01-24 add vigling
2025-01-24 add data record but with mistakes
2025-02-02 IR_module update
2025-02-03 bom file change
2025-02-04 version before cleaning
2025-02-05 after cleaning
2025-02-10 new feature - vigling
2025-02-16 new PCB start
    Yeah yeah I know, pushing into main, it'll be dealt with once I create PCB repo
2025-03-02 symbol library update
2025-03-05 edit ir start/stop
2025-03-25 little edits
